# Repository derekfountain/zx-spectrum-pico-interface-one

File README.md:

# ZX Spectrum Expansion System, Recreated

**Update August'26:
Following recent interest in this project I've been
making a few interfaces up so people can buy them. The [project page](https://www.derekfountain.org/zses.php)
on [my personal website](https://www.derekfountain.org/) has the details
on how to get hold of one.**

**<derek@scratters.com>**

## An Interface One / Microdrive Emulation for the ZX Spectrum

This device plugs into the back of a 48K ZX Spectrum and provides the
functionality of the original 1984 "ZX Spectrum Expansion System". It
emulates a ZX Interface One with 8 ZX Microdrives.

The device is completely compatible with all 1980s software. It uses no
ROM modifications or other hacks. To my knowledge there are no
limitations or caveats to its use.

The first version is complete and supports the ZX Microdrives as
designed; the RS232 and ZX Net features of the Interface One might follow.

The project is open source, open hardware design, distributed under the
GPL licence.

There's lots more information on the [project page](https://www.derekfountain.org/zses.php)
on [my website](https://www.derekfountain.org/).

Click through for a brief demonstration:

https://www.youtube.com/watch?v=kph2aS7qcVc

## Status

As of September 2023, version 1.0 is complete:

It is functionally complete:

* Spectrum can read and write all 8 microdrives
* Uses "MDR" image format for "cartridges", fully compatible with emulators
* Full ZX Interface One ROM support, all native BASIC commands and extensions work as designed
* MDR files loaded from, and saved back to, SD card
* User interface uses file selector to choose and "insert" a cartridge
* Cartridge eject, allowing cartridges to be changed as required
* Configuration file allows auto-insertion of selected cartridges at start up

I'd be interested to receive feedback from anyone who tries to build one.

[Derek Fountain](https://www.derekfountain.org/), September 2023

# Operation

It should be fairly obvious. Select the Microdrive with the rotary encoder, click the right
button to bring up the file selector, use the rotary to select a cartridge file, then click the right button
again. The left button cancels.

The file selector only brings up files named *.mdr, and it doesn't do subdirectories. This
could be improved.

If you create a file in the root of your SD card called zxes_config.txt (that's not a
typo, I have an issue open to rename that file to match the rest of the project) and
enter up to 8 lines, each with a filename giving the name of an MDR file on your SD card,
those cartridge images will be loaded into the Microdrives on startup. (Startup meaning the
Pico startup, not the Spectrum start up.)

# Build Guidance

If you want to have a go at building one, please ensure you check out the open issues first.
There are a few, um, anomalies, which you might want to consider or work around. If I do
another spin of the boards I should be able to clear these up.

That said...

The KiCad files for the main board are in /srom/srom.kicad_pro. (The project started off as a port
of my [Spectrum Pico ROM](https://github.com/derekfountain/zx-spectrum-pico-rom), and the directory
name got ported over.)

The KiCad files for the top board (the daughter board with the screen and buttons) are in
/ui_daughterboard/ui_daughterboard.kicad_pro.

The silver faceplate is a (non functional) PCB. I had JLCPCB make it up in aluminium. The design
for that is in with the case design: /3d_print/top_panel/top_panel.kicad_pro.

All my surface mount component footprints are metric 3216 sized (1206i). Those are easy to hand solder.

The OLED screen needs a SSD1306 chipset if you want to use my code. Be careful, some SSH1106
based screens are labelled SSD1306. Those won't work without modifications to the code.

I've used long legged header sockets (female) to raise the top board well up above the Picos. If you
use the normal ones they probably won't be tall enough, unless you choose not to socket the Picos.

## Bill of Materials

You will need:

2x [74LVC245 Bus transceiver](https://www.mouser.co.uk/ProductDetail/595-SN74LVC245ANSR)
Bus transceiver, used as a level shifter
<br>
1x [3216 SMD Diode](https://www.mouser.co.uk/ProductDetail/581-SD1206S040S2R0)
Schottky Diode for Pico input protection
<br>
1x [4075 OR gate](https://www.mouser.co.uk/ProductDetail/595-SN74HCS4075DR)
3-way 3-input OR gate
<br>
4x [3216 SMD 0.1uF capacitor](https://www.mouser.co.uk/ProductDetail/581-12065C104KAT4A)
Decoupling capacitor
<br>
1x [PMBT2222A SMD Transistor](https://www.mouser.co.uk/ProductDetail/771-PMBT2222A-T-R)
NPN Transistor for /RESET
<br>
2x [3216 SMD 1K Resistor](https://www.mouser.co.uk/ProductDetail/603-RT1206FRE071KL)
1K Resistor for /RESET and /ROMCS2 pulldown
<br>
8x [3216 SMD 150R Resistor](https://www.mouser.co.uk/ProductDetail/603-RT1206FRE07150RL)
150R Resistor for data bus protection
<br>
1x [3216 SMD 330R Resistor](https://www.mouser.co.uk/ProductDetail/YAGEO/RT1206FRE07330RL)
330R Resistor for LED current limitation
<br>
1x [APS6404L-3SQR-PSRAM64Mbit Serial DRAM](https://www.mouser.co.uk/ProductDetail/878-APS6404L-3SQR-SN)
8MB SPI DRAM. A 1MB chip would probably be adequate.
<br>

Also, from your parts bin:

3x Raspberry Pi Pico with pins and sockets if you want them
<br>
1x 3-pin header and socket
<br>
1x 6-pin header and socket
<br>
1x 10-pin header and socket
<br>
1x KY-040 rotary encoder. Mine came with a 90degree header pin which I replaced with a straight header
<br>
1x 90degree ZX Spectrum Edge Connector socket. I went for [this one](https://www.ebay.co.uk/itm/394156247495).
<br>
2x SPST switch. Any single pole, single throw switch should do, they are the reset buttons.
<br>
1x Push-push type SD card reader. I used [this one](https://www.ebay.co.uk/itm/133222265884).
<br>
1x 0.96" OLED display (SSD1306 based)
<br>
8x 3.0mm red LEDs. The faceplate holes are drilled for 3.0mm LEDs.

# Acknowledgements

[Andrew Menadue](http://trochilidae.blogspot.com/)
for his Pico to Pico PIO [communications code](https://github.com/blackjetrock/picoputer),
and his patiently answering so many of my questions.

Geoff Wearmouth and others for their superb [IF1 ROM disassembly](https://www.derekfountain.org/misc/spectrum/if1_2.txt), which I suspect I now understand better than them.

Gergely Szasz, Philip Kendall and Stuart Brady from the
[FUSE Emulator Project](https://sourceforge.net/projects/fuse-emulator/).
[This](https://sourceforge.net/p/fuse-emulator/fuse/ci/master/tree/peripherals/if1.c)
one source file probably saved me weeks of work.

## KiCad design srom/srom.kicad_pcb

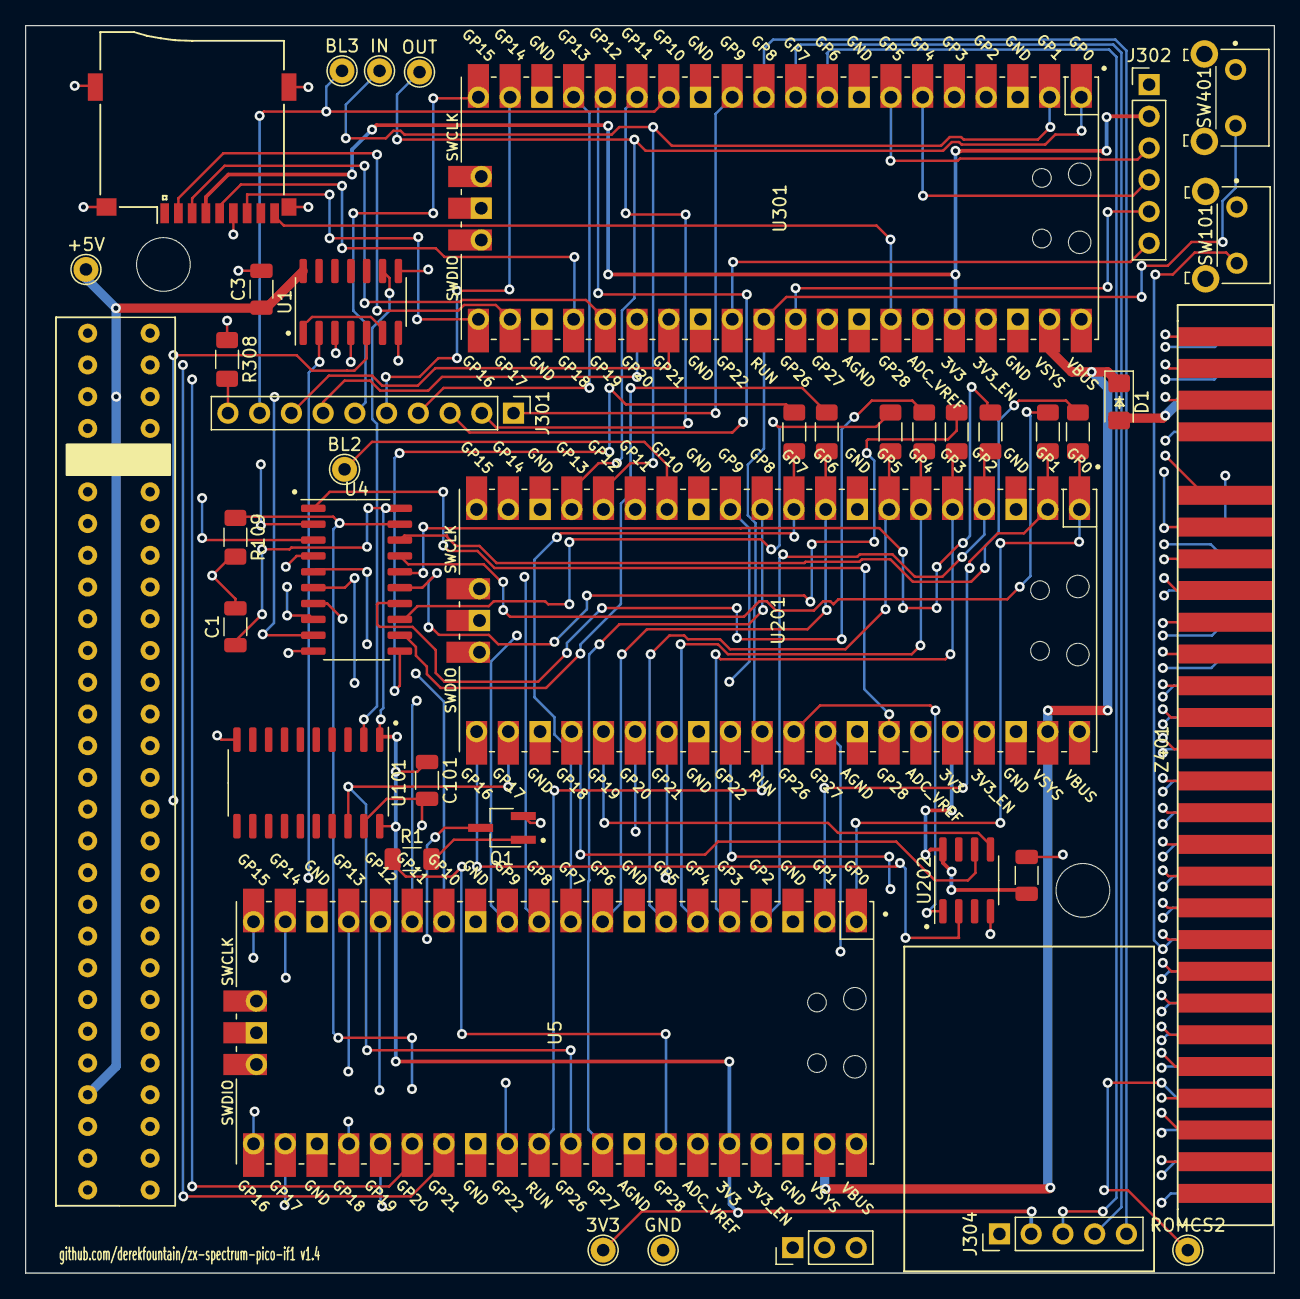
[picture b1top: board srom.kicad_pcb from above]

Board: 4 copper layers, 100.0 x 99.8 mm, 40 parts (0 on the bottom side), 107 nets.

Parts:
3V3: TestPoint_THTPad_D2.0mm_Drill1.0mm
+5V: TestPoint_THTPad_D2.0mm_Drill1.0mm
BL2, BL3: TestPoint_THTPad_D2.0mm_Drill1.0mm
C1, C3, C101, C201: C_Small; C_1206_3216Metric
D1: D_Schottky; D_1206_3216Metric_Pad1.42x1.75mm_HandSolder
GND: TestPoint_THTPad_D2.0mm_Drill1.0mm
IN: TestPoint_THTPad_D2.0mm_Drill1.0mm
J301: Conn_01x10_Female; PinHeader_1x10_P2.54mm_Vertical
J302: Conn_01x06_Female; PinHeader_1x06_P2.54mm_Vertical
J304: Conn_01x05_Female; PinHeader_1x05_P2.54mm_Vertical
OUT: TestPoint_THTPad_D2.0mm_Drill1.0mm
Q1: PMBT2222A; TSOT-23_HandSoldering
R1: 1K; R_1206_3216Metric_Pad1.30x1.75mm_HandSolder
R101, R102, R103, R104, R105, R106, R107, R108: R150; R_1206_3216Metric_Pad1.30x1.75mm_HandSolder
R109: 1KR; R_1206_3216Metric_Pad1.30x1.75mm_HandSolder
R308: R330; R_1206_3216Metric_Pad1.30x1.75mm_HandSolder
ROMCS2: TestPoint_THTPad_D2.0mm_Drill1.0mm
SW101, SW401: SW_SPST; SW_Tactile_SKHH_Angled
U1: 4075; SOIC-14_3.9x8.7mm_P1.27mm
U4, U101: 74LS245; SO-20_5.3x12.6mm_P1.27mm
U5: Pico-1 ROM; RPi_Pico_SMD_TH
U201: Pico-2 IO; RPi_Pico_SMD_TH
U202: APS6404L-3SQR_PSRAM64Mbit; SOIC-8_3.9x4.9mm_P1.27mm
U301: Pico-3 UI; RPi_Pico_SMD_TH
XS301: 502p_SD_ebay-uSD-push_push_SMD-pak_breakout; Conn_uSDcard
Z1: ZX48Bus; ZX_Bus_Pin_Header
Z401: ZX48Bus; ZX_Bus_Edge_Connector

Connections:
3V3_PICO1: 3V3.1, C1.1, C101.1, J304.2, U4.20 (VCC), U5.36 (3V3), U101.1 (A->B), U101.20 (VCC)
3V3_PICO2: C201.1, U201.36 (3V3), U202.8 (VCC)
3V3_PICO3: J302.2, U301.36 (3V3), XS301.4 (Vdd)
+5V: +5V.1, C3.1, D1.2 (A), U1.14 (VDD), Z1.B3 (+5v), Z1.B25 (~ROMCS), Z401.B3 (+5v)
ACTION_SW: J302.5, U301.31 (GPIO26_ADC0)
CANCEL_SW: J302.6, U301.29 (GPIO22)
D0: R101.2, U5.1 (GPIO0), U201.1 (GPIO0)
D1: R102.2, U5.2 (GPIO1), U201.2 (GPIO1)
D2: R103.2, U5.4 (GPIO2), U201.4 (GPIO2)
D3: R104.2, U5.5 (GPIO3), U201.5 (GPIO3)
D4: R105.2, U5.6 (GPIO4), U201.6 (GPIO4)
D5: R106.2, U5.7 (GPIO5), U201.7 (GPIO5)
D6: R107.2, U5.9 (GPIO6), U201.9 (GPIO6)
D7: R108.2, U5.10 (GPIO7), U201.10 (GPIO7)
DBUS_DIRECTION: U4.1 (A->B), U201.34 (GPIO28_ADC2)
GND: C1.2, C3.2, C101.2, C201.2, GND.1, J302.1, J304.1, Q1.2 (E), R109.2, R308.1, SW101.1 (A), SW401.1 (A), U1.7 (VSS), U1.8, U4.10 (GND), U5.3 (GND), U5.8 (GND), U5.13 (GND), U5.18 (GND), U5.23 (GND), U5.28 (GND), U5.33 (AGND), U5.38 (GND), U5.42 (GND), U101.10 (GND), U101.19 (CE), U201.3 (GND), U201.8 (GND), U201.13 (GND), U201.18 (GND), U201.23 (GND), U201.28 (GND), U201.33 (AGND), U201.38 (GND), U201.42 (GND), U202.4 (VSS), U301.3 (GND), U301.8 (GND), U301.13 (GND), U301.18 (GND), U301.23 (GND), U301.28 (GND), U301.33 (AGND), U301.38 (GND), U301.42 (GND), XS301.6 (GND), Z1.B6 (GND), Z1.B7 (GND), Z1.B14 (GND), Z401.B6 (GND), Z401.B7 (GND), Z401.B14 (GND)
IF1_PORT_ACTIVE: U5.32 (GPIO27_ADC1), U201.11 (GPIO8)
MD0_LED: J301.1, U301.12 (GPIO9)
MD1_LED: J301.2, U301.15 (GPIO11)
MD2_LED: J301.3, U301.16 (GPIO12)
MD3_LED: J301.4, U301.17 (GPIO13)
MD4_LED: J301.5, U301.19 (GPIO14)
MD5_LED: J301.6, U301.20 (GPIO15)
MD6_LED: J301.7, U301.26 (GPIO20)
MD7_LED: J301.8, U301.27 (GPIO21)
unnamed: J301.10, R308.2
unnamed: Q1.1 (B), R1.2
unnamed: R101.1, U4.18 (B0)
unnamed: R102.1, U4.17 (B1)
unnamed: R103.1, U4.16 (B2)
unnamed: R104.1, U4.15 (B3)
unnamed: R105.1, U4.14 (B4)
unnamed: R106.1, U4.13 (B5)
unnamed: R107.1, U4.12 (B6)
unnamed: R108.1, U4.11 (B7)
OLED_SCK: J302.3, U301.7 (GPIO5)
OLED_SDA: J302.4, U301.6 (GPIO4)
PICOS_RUN: SW401.2 (B), U5.30 (RUN), U201.30 (RUN), U301.30 (RUN)
PICO_PWR: D1.1 (K), U5.39 (VSYS), U201.39 (VSYS), U301.39 (VSYS)
PICO_RESET_Z80: R1.1, U5.34 (GPIO28_ADC2)
ROMCS2: R109.1, ROMCS2.1, U4.19 (CE), Z401.B25 (~ROMCS)
ROM_ACCESS_INV: U1.1, U1.6
ROM_READ_INV: U1.9, U101.2 (A0)
ROM_READ_INV_3V3: U5.31 (GPIO26_ADC0), U101.18 (B0), U201.22 (GPIO17)
ROT_CLK_A: J304.5, U301.11 (GPIO8)
ROT_DT_B: J304.4, U301.10 (GPIO7)
ROT_SW: J304.3, U301.9 (GPIO6)
SD_CARD_DETECT: U301.34 (GPIO28_ADC2), XS301.9 (CD)
SPI0_PSRAM_CLK: U201.24 (GPIO18), U202.6 (SCLK)
SPI0_PSRAM_MISO: U201.21 (GPIO16), U202.2 (SO/SIO)
SPI0_PSRAM_MOSI: U201.25 (GPIO19), U202.5 (SI/SIO)
SPI0_PSRAM_SLAVE_ENABLE: U201.31 (GPIO26_ADC0), U202.1 (~CE)
SPI0_SD_CLK: U301.24 (GPIO18), XS301.5 (CLK)
SPI0_SD_MISO: U301.21 (GPIO16), XS301.7 (DO/DAT0)
SPI0_SD_MOSI: U301.25 (GPIO19), XS301.3 (DI/CMD)
SPI0_SD_SLAVE_ENABLE: U301.22 (GPIO17), XS301.2 (CS/DAT3)
TEST_BLIPPER_P2: BL2.1, U201.14 (GPIO10)
TEST_BLIPPER_P3: BL3.1, J301.9, U301.14 (GPIO10)
UI_LINKIN: IN.1, U201.16 (GPIO12), U301.2 (GPIO1)
UI_LINKOUT: OUT.1, U201.17 (GPIO13), U301.1 (GPIO0)
ZX9V: Z1.B4 (+9V), Z401.B4 (+9V)
ZX12V: Z1.A22 (+12V), Z401.A22 (+12V)
ZX12VAC: Z1.A23 (+12VAC), Z401.A23 (+12VAC)
ZXA0: U5.11 (GPIO8), Z1.B9 (A0), Z401.B9 (A0)
ZXA1: U5.12 (GPIO9), Z1.B10 (A1), Z401.B10 (A1)
ZXA2: U5.14 (GPIO10), Z1.B11 (A2), Z401.B11 (A2)
ZXA3: U5.15 (GPIO11), U201.12 (GPIO9), Z1.B12 (A3), Z401.B12 (A3)
ZXA4: U5.16 (GPIO12), Z1.B24 (A4), Z401.B24 (A4)
ZXA5: U5.17 (GPIO13), Z1.B23 (A5), Z401.B23 (A5)
ZXA6: U5.19 (GPIO14), Z1.B22 (A6), Z401.B22 (A6)
ZXA7: U5.20 (GPIO15), Z1.B21 (A7), Z401.B21 (A7)
ZXA8: U5.21 (GPIO16), Z1.A26 (A8), Z401.A26 (A8)
ZXA9: U5.22 (GPIO17), Z1.B27 (A9), Z401.B27 (A9)
ZXA10: U5.24 (GPIO18), Z1.A27 (A10), Z401.A27 (A10)
ZXA11: U5.25 (GPIO19), Z1.B28 (A11), Z401.B28 (A11)
ZXA12: U5.26 (GPIO20), Z1.B2 (A12), Z401.B2 (A12)
ZXA13: U5.27 (GPIO21), Z1.A2 (A13), Z401.A2 (A13)
ZXA14: U1.4, Z1.B1 (A14), Z401.B1 (A14)
ZXA15: U1.3, Z1.A1 (A15), Z401.A1 (A15)
ZXBUSACK: Z1.B26 (~BUSACK), Z401.B26 (~BUSACK)
ZXBUSRQ: Z1.B19 (~BUSRQ), Z401.B19 (~BUSRQ)
ZXCLK: Z1.B8 (CLK), Z401.B8 (CLK)
ZXD0: U4.2 (A0), Z1.A6 (D0), Z401.A6 (D0)
ZXD1: U4.3 (A1), Z1.A7 (D1), Z401.A7 (D1)
ZXD2: U4.4 (A2), Z1.A8 (D2), Z401.A8 (D2)
ZXD3: U4.5 (A3), Z1.A11 (D3), Z401.A11 (D3)
ZXD4: U4.6 (A4), Z1.A12 (D4), Z401.A12 (D4)
ZXD5: U4.7 (A5), Z1.A10 (D5), Z401.A10 (D5)
ZXD6: U4.8 (A6), Z1.A9 (D6), Z401.A9 (D6)
ZXD7: U4.9 (A7), Z1.A3 (D7), Z401.A3 (D7)
ZXHALT: Z1.A15 (~HALT), Z401.A15 (~HALT)
ZXINT: Z1.A13 (~INT), Z401.A13 (~INT)
ZXIORQ: U201.26 (GPIO20), Z1.A17 (~IORQ), Z401.A17 (~IORQ)
ZXIORQGE: Z1.B13 (~IORQGE), Z401.B13 (~IORQGE)
ZXM1: U5.29 (GPIO22), Z1.A24 (~M1), Z401.A24 (~M1)
ZXMIN5V: Z1.A20 (-5V), Z401.A20 (-5V)
ZXMREQ: U1.5, Z1.A16 (~MREQ), Z401.A16 (~MREQ)
ZXNMI: Z1.A14 (~NMI), Z401.A14 (~NMI)
ZXRD: U1.2, U201.27 (GPIO21), Z1.A18 (~RD), Z401.A18 (~RD)
ZXRESET: Q1.3 (C), SW101.2 (B), Z1.B20 (~RESET), Z401.B20 (~RESET)
ZXRFSH: Z1.A25 (~RFSH), Z401.A25 (~RFSH)
ZXU: Z1.B18 (U), Z401.B18 (U)
ZXV: Z1.B17 (V), Z401.B17 (V)
ZXVIDEO: Z1.B15 (VIDEO), Z401.B15 (VIDEO)
ZXWAIT: U201.32 (GPIO27_ADC1), Z1.A21 (~WAIT), Z401.A21 (~WAIT)
ZXWR: U201.29 (GPIO22), Z1.A19 (~WR), Z401.A19 (~WR)
ZXY: Z1.B16 (Y), Z401.B16 (Y)

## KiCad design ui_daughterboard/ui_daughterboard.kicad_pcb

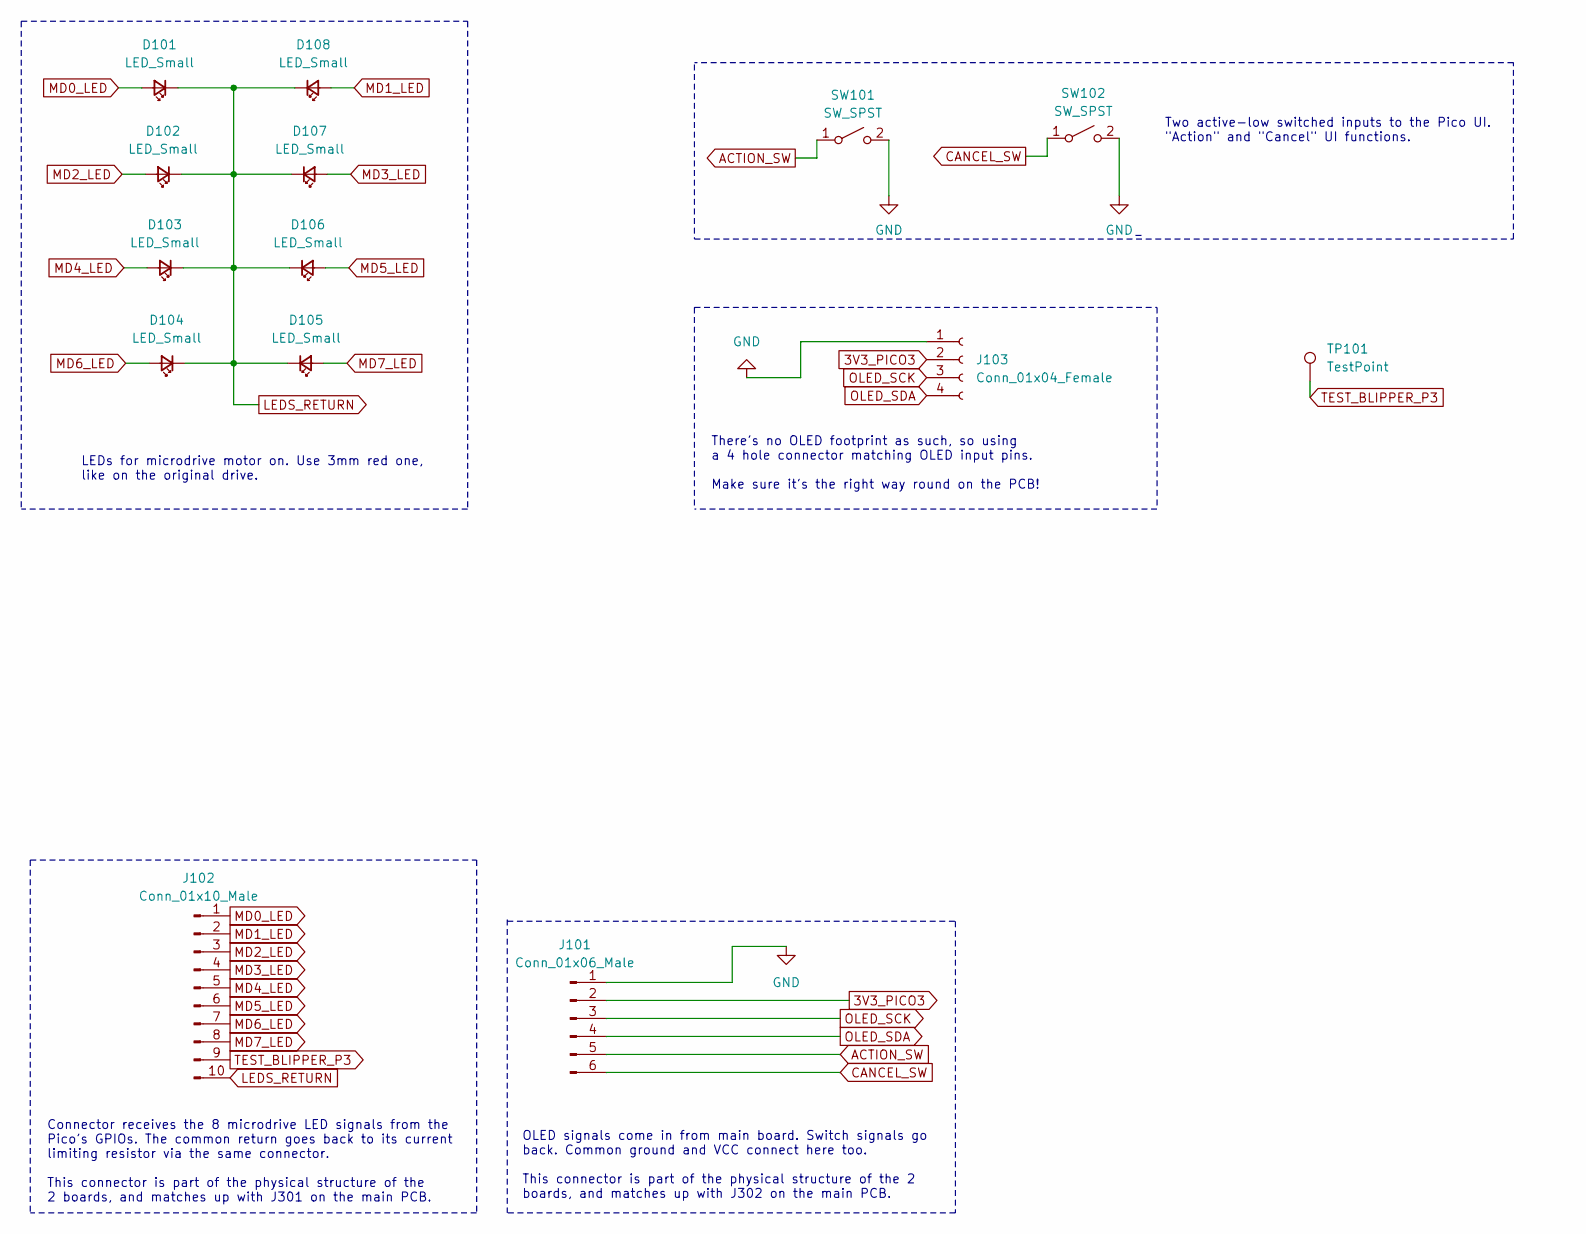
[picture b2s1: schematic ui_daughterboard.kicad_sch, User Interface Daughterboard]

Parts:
D101, D102, D103, D104, D105, D106, D107, D108: LED_Small; LED_D3.0mm
J101: Conn_01x06_Male; PinHeader_1x06_P2.54mm_Vertical
J102: Conn_01x10_Male; PinHeader_1x10_P2.54mm_Vertical
J103: Conn_01x04_Female; PinHeader_1x04_P2.54mm_Vertical
SW101, SW102: SW_SPST; SW_PUSH_6mm_H4.3mm
TP101: TestPoint; TestPoint_THTPad_D2.0mm_Drill1.0mm

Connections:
3V3_PICO3: J101.2, J103.2; also elsewhere on the board
ACTION_SW: J101.5, SW101.1 (A)
CANCEL_SW: J101.6, SW102.1 (A)
GND: J101.1, J103.1, SW101.2 (B), SW102.2 (B); also elsewhere on the board
LEDS_RETURN: D101.1 (K), D102.1 (K), D103.1 (K), D104.1 (K), D105.1 (K), D106.1 (K), D107.1 (K), D108.1 (K), J102.10
MD0_LED: D101.2 (A), J102.1
MD1_LED: D108.2 (A), J102.2
MD2_LED: D102.2 (A), J102.3
MD3_LED: D107.2 (A), J102.4
MD4_LED: D103.2 (A), J102.5
MD5_LED: D106.2 (A), J102.6
MD6_LED: D104.2 (A), J102.7
MD7_LED: D105.2 (A), J102.8
OLED_SCK: J101.3, J103.3
OLED_SDA: J101.4, J103.4
TEST_BLIPPER_P3: J102.9, TP101.1

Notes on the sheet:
Connector receives the 8 microdrive LED signals from the Pico's GPIOs. The common return goes back to its current limiting resistor via the same connector. This connector is part of the physical structure of the 2 boards, and matches up with J301 on the main PCB.
LEDs for microdrive motor on. Use 3mm red one, like on the original drive.
OLED signals come in from main board. Switch signals go back. Common ground and VCC connect here too. This connector is part of the physical structure of the 2 boards, and matches up with J302 on the main PCB.
There's no OLED footprint as such, so using a 4 hole connector matching OLED input pins. Make sure it's the right way round on the PCB!
Two active-low switched inputs to the Pico UI. "Action" and "Cancel" UI functions.

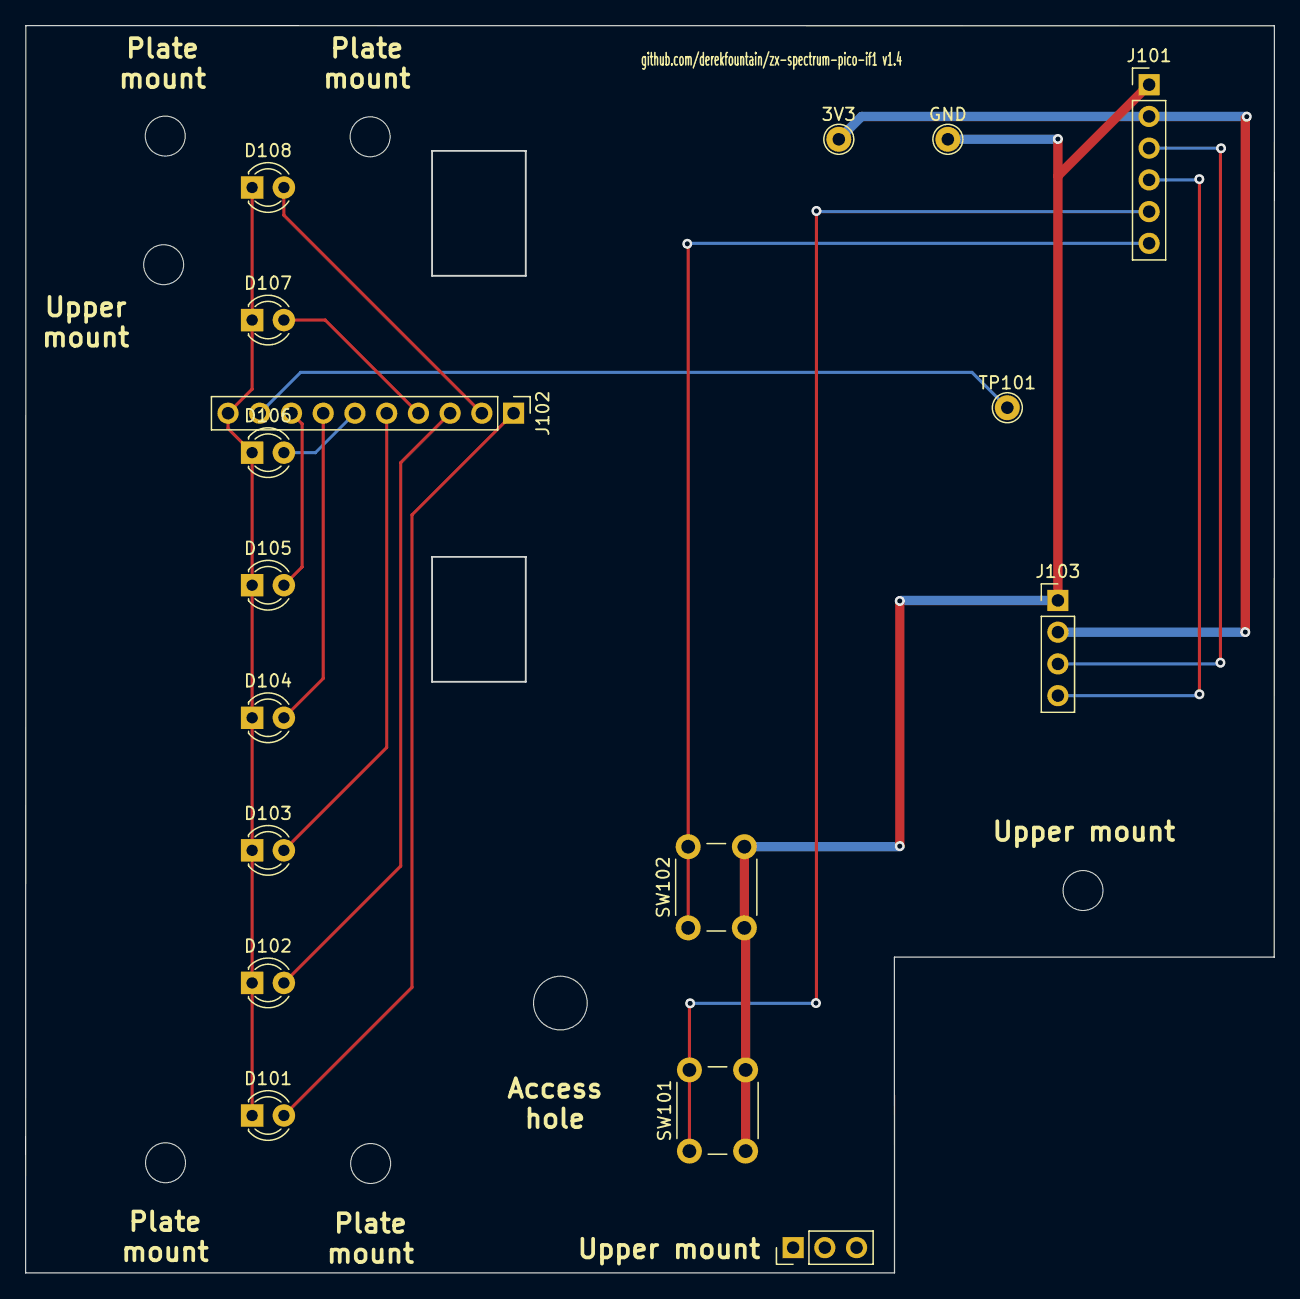
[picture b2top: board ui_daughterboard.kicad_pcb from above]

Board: 2 copper layers, 100.0 x 99.9 mm, 16 parts (0 on the bottom side), 16 nets.

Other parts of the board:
3V3: TestPoint; TestPoint_THTPad_D2.0mm_Drill1.0mm
GND: TestPoint; TestPoint_THTPad_D2.0mm_Drill1.0mm

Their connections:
3V3_PICO3: 3V3.1; also elsewhere on the board
GND: GND.1; also elsewhere on the board

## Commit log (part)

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2023-02-06 initial, based on pico rom project
2023-02-09 add IO and UI schematics
2023-02-11 schematics complete for IO and UI picos
2023-02-12 first draft pcb layout
2023-02-12 design rules checker happy
2023-02-12 ready for fab
2023-02-22 fix 2222 transistor footprint on PCB
2023-02-28 first draft of board working as a ROM emulator
2023-02-28 change the level shifter enabling from /CE to DIR as per original design for this board. confirm still works
2023-02-28 tidy ups, remove address recorder code
2023-03-01 update schema and layout to match working ROM emulation board. 2 level shifters removed here
2023-03-01 break out the 3V3 supplies into separate ones
2023-03-01 drive the databus level shifter DIR pin from pico1 GPIO
2023-03-01 rename firmware to firmware-rom
2023-03-02 first build of the IO firmware. contains 'blink'. works though
2023-03-02 IO pico now switching the level shifter direction for memory reads
2023-03-02 correct result from a PRINT IN 223 sometimes appears from 2nd core
2023-03-02 tidy up, bring code back to core0, still has first time failure issue
2023-03-02 add the databus optimisation in
2023-03-03 fix input byte bit shifting
2023-03-03 rethink needed, the ROM DIR switch is time critical and one core can't do it all
2023-03-03 backed out the array idea for now
2023-03-04 lots of experimental dual core stuff, most of it needs to come out, some might be useful
2023-03-06 finally worked out the logic behind E7/EF reads and writes on the buses
2023-03-06 tidy up, test for IN/OUT port 231 works, but the initial failure is still there
2023-03-07 add test code
2023-03-07 run from ram, solves initial performance problem
2023-03-07 start the emulation code, no idea where this is going yet
2023-03-07 some of the FUSE microdrive code ported in, it compiles, this won't run and i haven't tried it
2023-03-08 control byte ported. compiles.
2023-03-08 all primitives ported over, compiles, no chance of it working yet
2023-03-08 CAT 1 now gives MD not found error, which is an improvement
2023-03-13 loading a pre-saved file works
2023-03-13 manic miner test image
2023-03-13 single core (for now), loads mm
2023-03-16 remove dual core stuff for now, tracing added to the rom emulator, remove cruft from IO emulator. CAT still broken
2023-03-20 need to run ROM code from Pico RAM
2023-03-20 more tidying up, gitignores added, mm MDR image
2023-03-20 CAT command works, not sure why
2023-03-20 start on write protect
2023-03-20 reinsert the checks in port_ctr_in()
2023-03-21 remove what appears to be unused code from libspectrum_microdrive code
2023-03-21 more clean ups, comments, unused code removal
2023-03-21 small tweaks, saving isn't going to be fast enough
2023-03-21 added PIO blink test code
2023-03-22 first draft of doing the MREQ DIR switch on PIO
2023-03-22 this appears to be the DIR via PIO solution, write code still needs moving to core1
2023-03-22 moved write data code to core1, SAVE and FORMAT still not working
2023-03-23 SAVE works, but only with if1 code commented out for speed
2023-03-23 move the microdrives_restart() to the second core, saves now work
2023-03-23 back to MM image, loads without copy to ram, format still broken
2023-03-24 first use of WAIT line
2023-03-26 comments, FORMAT still not working
2023-03-27 add 8 MDR images to resources
2023-03-27 8 MDR test images now in the build
2023-03-28 254 sector MD images in flash, OOM
2023-03-28 revert to 180 sector images for now
2023-03-28 first draft of multi-drive code. messy, save is broken. need to rethink this
2023-03-29 enable usb. doesn't really work, interrupts are the issue. worth keeping, will turn off again
2023-03-29 bail out of USB printfs point. can't think of anything else to make it work
2023-03-29 broken multi-drive code, bits of usb, moved main to core1
2023-03-29 the dog's breakfast commit. some of this will be useful. back out and do it again.
2023-03-29 keep the stdio work, which might be useful even if it doesn't work ATM. keep the changes to move the main code into the second core
2023-03-30 some careful work on the drive motor selection
2023-03-30 initial 'shift register' and active microdrive work done
2023-03-30 strip out all the libspectrum cruft, remove internals.h
2023-03-30 more clearing out of the fuse code, microdrive.c now gone
2023-03-30 remove data array from cartridge structure
2023-03-30 removed the single md image, replaced with array of 8 currently identical ones
2023-03-31 lots more cleanups, all 8 test mdr images in flash
2023-03-31 read from all 8 MDs now working
2023-03-31 try to clarify exactly what data are what type
2023-04-03 add some tracing to the paging. it's far too slow, 600ms with /WAIT active. also fix hard power up issue
2023-04-03 run some timings on the flash operations, added comments
2023-04-04 add some rudimentary tracing, minor tweaks
2023-04-04 use DMA to move cartridge image in from flash, makes little difference
2023-04-04 seems like the erratic startup issue was removing the blinking LED before the second core launch. no idea why. i added a 100ms pause, that seems to fix it too
2023-04-13 update schematic to match my modified prototype hardware
2023-04-14 start v1.3 of board, level shifter required
2023-04-14 move the ZXWAIT signal on pico2 off the SP1 connection. matches latest hardware
2023-04-14 SPI memory inits OK, last GPIO used up. schematic needs updating
2023-04-15 initial work with SPI RAM based images. 8 cartridges reading and writing
2023-04-15 update schematic to match current hardware
2023-04-15 code and schematic match final hardware for board #1, time to have a new one built
2023-04-16 move PIO init up so the ROM emulation works even if the SPI memory doesn't
2023-04-16 remove address lines from pico2, replace with a signal from pico1, frees GPIOs on pico2
2023-04-17 start updating schematic for next board
2023-04-17 more work on the layout of board 2
2023-04-18 v1.3 of the board off to production
2023-04-20 errata updates
2023-04-20 attempt tracing to PSRAM, doesn't really work. will back out
2023-04-20 tracing back in a RAM buffer. hunt for FORMAT issue continues
2023-04-23 FORMAT bug finally nailed
2023-04-29 prototype board2 working for LOAD, SAVE and FORMAT
2023-05-02 switch back to 254 sector test images
2023-05-02 remove the stdio messaging remnants
2023-05-02 initialise UI firmware
2023-05-03 bit of research, working out pico to pico SPI speeds and config. works at 5MHz
2023-05-05 message on OLED screen, fix needed on board
2023-05-06 rotarty encoder working, connector is reversed, needs fixing
2023-05-06 add SD card library, simple example working, no mods needed to board
2023-05-08 crowbar in the changes to demo the UART link works. not sure where to go from here
2023-05-09 move test images from IO flash to UI flash
2023-05-10 tidy up headers, create common directory, remove soft links
2023-05-10 remove the page size idea, that won't work with variable MDR sizes. sort write protect out
2023-05-11 test image now loads from SD card. clean up the IO pico code a bit more, remove all flash references
2023-05-11 tidy ups in the IO code
2023-05-11 add a preamble to the CMD transmission, try to help picos get back in sync after programming
2023-05-12 separate out work into core1, add work queue structure
2023-05-12 add the request status command, showed up a problem with high speed UART, slowed to 115200, can't work out what's going on
2023-05-14 bit of a hack to fix an issue with the work queue
2023-05-14 remove left over conversion table line, in conditional compilation
2023-05-14 MVP test setup, load specifically named MDR files on start up
2023-05-14 add very basic checksum to MDR image transfer
2023-05-14 return microdrive status to UI pico on regular poll
2023-05-15 data written to cartridge is now transferred back to the UI pico and written to SD card
2023-05-16 add SD card detect to hardware
2023-05-16 break out the oled display code
2023-05-17 add some LEDs to schematic
2023-05-18 tentative start on a GUI
2023-05-18 sort out inverted text and boxes
2023-05-18 introduce a GUI state machine
2023-05-19 lots of GUI status screen work, FSM code still not properly working
2023-05-19 enable the rotary encoder
2023-05-19 break entry_fn bindings out from map
2023-05-20 update README with a few details
2023-05-20 display now shows inserted file details
2023-05-21 add inserting status to display
2023-05-21 feedback for saving changed MD data now working
2023-05-22 critical section around FSM stimulus processing. also change to stimulus queue
2023-05-23 lots of work getting the GUI FSM workable
2023-05-23 tidyups in the FSM code, get FSM files generated from cmake
2023-05-24 add 2 switches as buttons for the UI
2023-05-25 eject working
2023-06-10 make a start on filename selection, not sure about this yet
2023-06-11 transputer link in, in place of uart
2023-06-11 tidy up the UI to IO link code
2023-06-11 update schematic, remove uart UI/IO link, replace with PIO link
2023-06-13 clear file list screen if insertion is cancelled
2023-06-13 crude, hardcoded file selector code working
2023-06-14 MDR insert working, albeit from a hardcoded list of filenames
2023-06-14 add original ZX Spectrum Expansion System cartridge images
2023-06-14 config file mechanism now in place, sample SD card image added
2023-06-15 update errata, time to sort out the next iteration of the board
2023-06-17 add rear edge schematic, RUN switch, ROMCS2 signal
2023-06-18 8 LEDs on UI Pico's GPIOs, 2 tested and working
2023-06-18 design files for the top panel
2023-06-19 remove test point connectors, no needed on next board (famous last words)
2023-06-22 board layout work, 4 layers
2023-06-22 board layout, across board tracks
2023-06-22 more work on the new pcb, i think i have the basic layout now
2023-06-22 layout has no rats nest and no errors
2023-06-23 clean ups, test points
2023-06-23 final pcb? about to copy layout for daughterboard
2023-06-25 lots more work to finalise the board pre-fab
2023-06-25 v1.4 final, gerbers off for fabrication
2023-06-28 add a basic error status system to the IO pico
2023-06-29 remove checksum from ui to io command
2023-06-29 add 16 bit checksum to UI->IO MDR transfer
2023-06-30 change request status to singleton
2023-06-30 make IO init structure static
2023-06-30 remove MDR test init code
2023-06-30 remove dynamic memory allocation of filename in insert code
2023-06-30 remove dynamic memory allocation of request MDR data structure
2023-07-01 fix the filename handling
2023-07-01 handle SD card with no MDR files
2023-07-04 fix the invert text issue, bit of a mess this ssd1306 code
2023-07-04 tidy ups in the GUI
2023-07-04 make a start on the SD card detection
2023-07-05 SD card ejection corner case
2023-07-08 3d print lower case first design
2023-07-13 new board tweaks, lower part of case pretty much done
2023-07-14 more 3d print work, spacers
2023-07-14 fix LED wiring sequence
2023-07-14 tweak the state machine to make the rotary encoder direction as i expect it. not sure though
2023-07-17 final case work, at least for now
2023-07-18 added frame for the little screen
2023-07-18 final 3d print bits
2023-07-19 add some images
2023-07-20 sort out the YT link
2023-08-07 Add stable binaries
2023-10-05 Credit the correct authors for the IF1 disassembly
    While I appreciate the acknowledgement, the only credit I can take for the IF1
    disassembly is for hosting it on my server. I had no part in creating it.
    The original page where this disassembly was hosted listed Geoff Wearmouth as
    the maintainer. There is also a comment at the end of the linked file that
    credits others with specific parts of the documentation. It is them who should
    get the credit for their excellent work.
2023-12-10 Add files via upload
    Made a Slot for rear expantion connector and shortened board abit for a better fit in the zx Spectrum
2023-12-10 Add files via upload
    Modified Top and Bottom 3d printed Case.
2026-05-21 Update README, May 2026
